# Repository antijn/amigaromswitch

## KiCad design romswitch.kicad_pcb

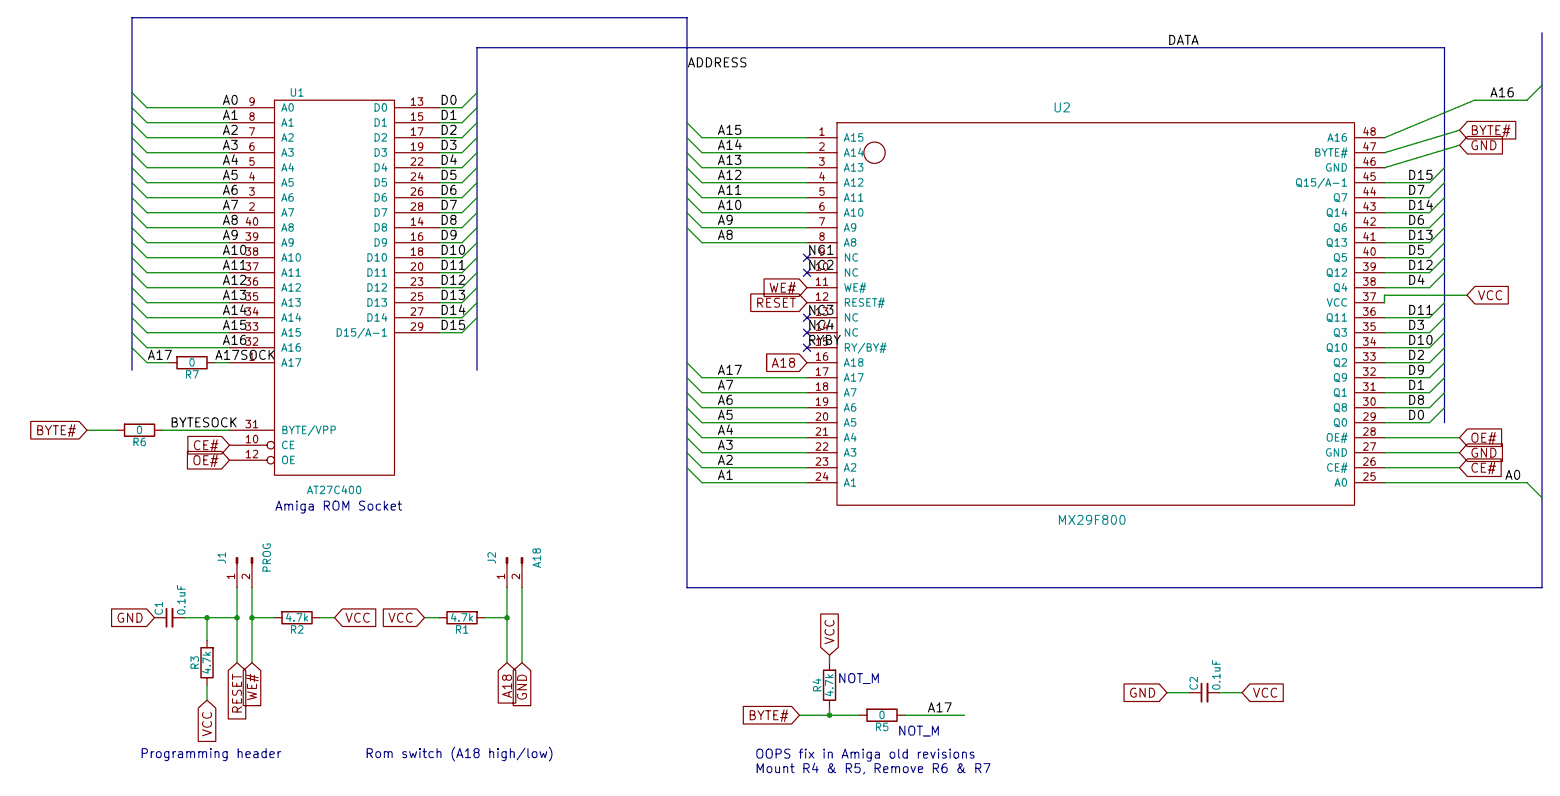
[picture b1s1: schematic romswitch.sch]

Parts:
C1, C2: 0.1uF; C_0603_HandSoldering
J1: PROG; Pin_Header_Angled_1x02_Pitch2.54mm
J2: A18; Pin_Header_Angled_1x02_Pitch2.54mm
R1, R2, R3, R4: 4.7k; R_0603_HandSoldering
R5, R6, R7: 0; R_0603_HandSoldering
U1: AT27C400; DIP-40_W15.24mm_Socket_LongPads
U2: MX29F800; TSOP-I-48_18.4x12mm_Pitch0.5mm

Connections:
/A0: U1.9 (A0), U2.25 (A0)
/A1: U1.8 (A1), U2.24 (A1)
/A2: U1.7 (A2), U2.23 (A2)
/A3: U1.6 (A3), U2.22 (A3)
/A4: U1.5 (A4), U2.21 (A4)
/A5: U1.4 (A5), U2.20 (A5)
/A6: U1.3 (A6), U2.19 (A6)
/A7: U1.2 (A7), U2.18 (A7)
/A8: U1.40 (A8), U2.8 (A8)
/A9: U1.39 (A9), U2.7 (A9)
/A10: U1.38 (A10), U2.6 (A10)
/A11: U1.37 (A11), U2.5 (A11)
/A12: U1.36 (A12), U2.4 (A12)
/A13: U1.35 (A13), U2.3 (A13)
/A14: U1.34 (A14), U2.2 (A14)
/A15: U1.33 (A15), U2.1 (A15)
/A16: U1.32 (A16), U2.48 (A16)
/A17: R5.1, R7.2, U2.17 (A17)
/A17SOCK: R7.1, U1.1 (A17)
/BYTESOCK: R6.1, U1.31 (BYTE/VPP)
/D0: U1.13 (D0), U2.29 (Q0)
/D1: U1.15 (D1), U2.31 (Q1)
/D2: U1.17 (D2), U2.33 (Q2)
/D3: U1.19 (D3), U2.35 (Q3)
/D4: U1.22 (D4), U2.38 (Q4)
/D5: U1.24 (D5), U2.40 (Q5)
/D6: U1.26 (D6), U2.42 (Q6)
/D7: U1.28 (D7), U2.44 (Q7)
/D8: U1.14 (D8), U2.30 (Q8)
/D9: U1.16 (D9), U2.32 (Q9)
/D10: U1.18 (D10), U2.34 (Q10)
/D11: U1.20 (D11), U2.36 (Q11)
/D12: U1.23 (D12), U2.39 (Q12)
/D13: U1.25 (D13), U2.41 (Q13)
/D14: U1.27 (D14), U2.43 (Q14)
/D15: U1.29 (D15/A-1), U2.45 (Q15/A-1)
/NC1: U2.9 (NC)
/NC2: U2.10 (NC)
/NC3: U2.13 (NC)
/NC4: U2.14 (NC)
/RYBY: U2.15 (RY/BY#)
A18: J2.1, R1.2, U2.16 (A18)
BYTE#: R4.1, R5.2, R6.2, U2.47 (BYTE#)
CE#: U1.10 (CE), U2.26 (CE#)
GND: C1.1, C2.1, J2.2, U1.11 (GND), U1.30 (GND), U2.27 (GND), U2.46 (GND)
OE#: U1.12 (OE), U2.28 (OE#)
RESET: C1.2, J1.1, R3.2, U2.12 (RESET#)
VCC: C2.2, R1.1, R2.1, R3.1, R4.2, U1.21 (VCC), U2.37 (VCC)
WE#: J1.2, R2.2, U2.11 (WE#)

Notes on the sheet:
OOPS fix in Amiga old revisions Mount R4 & R5, Remove R6 & R7
Rom switch (A18 high/low)
Programming header
Amiga ROM Socket
NOT_M

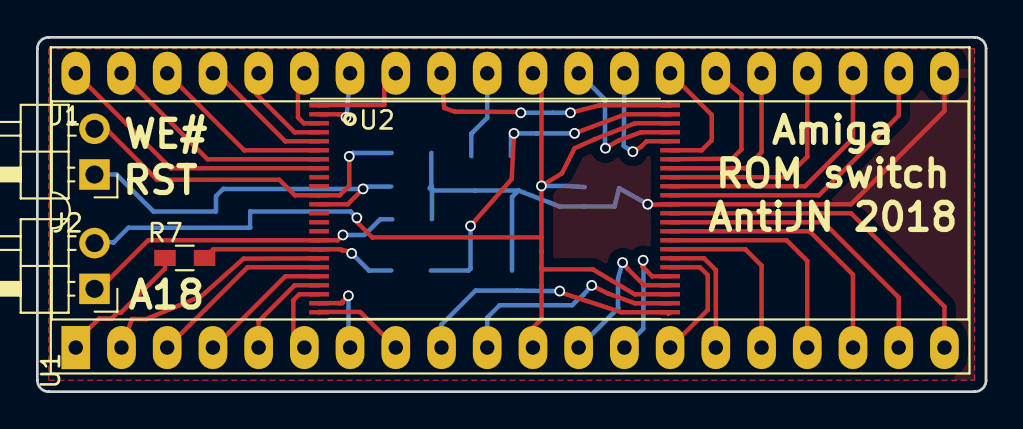
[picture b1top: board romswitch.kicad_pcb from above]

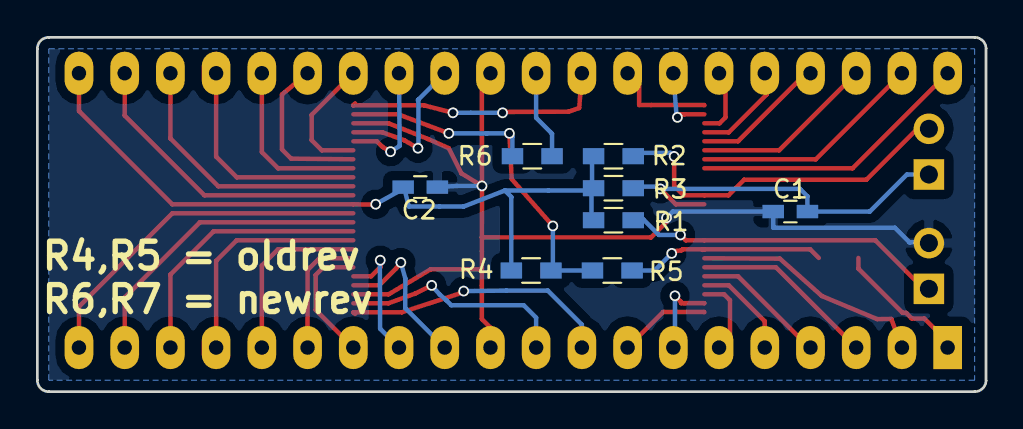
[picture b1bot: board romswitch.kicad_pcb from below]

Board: 2 copper layers, 52.7 x 19.7 mm, 13 parts (8 on the bottom side), 44 nets.

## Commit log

2018-04-09 First revision
2018-04-09 Print materials
2018-04-09 Add Macronix library, png snaps
